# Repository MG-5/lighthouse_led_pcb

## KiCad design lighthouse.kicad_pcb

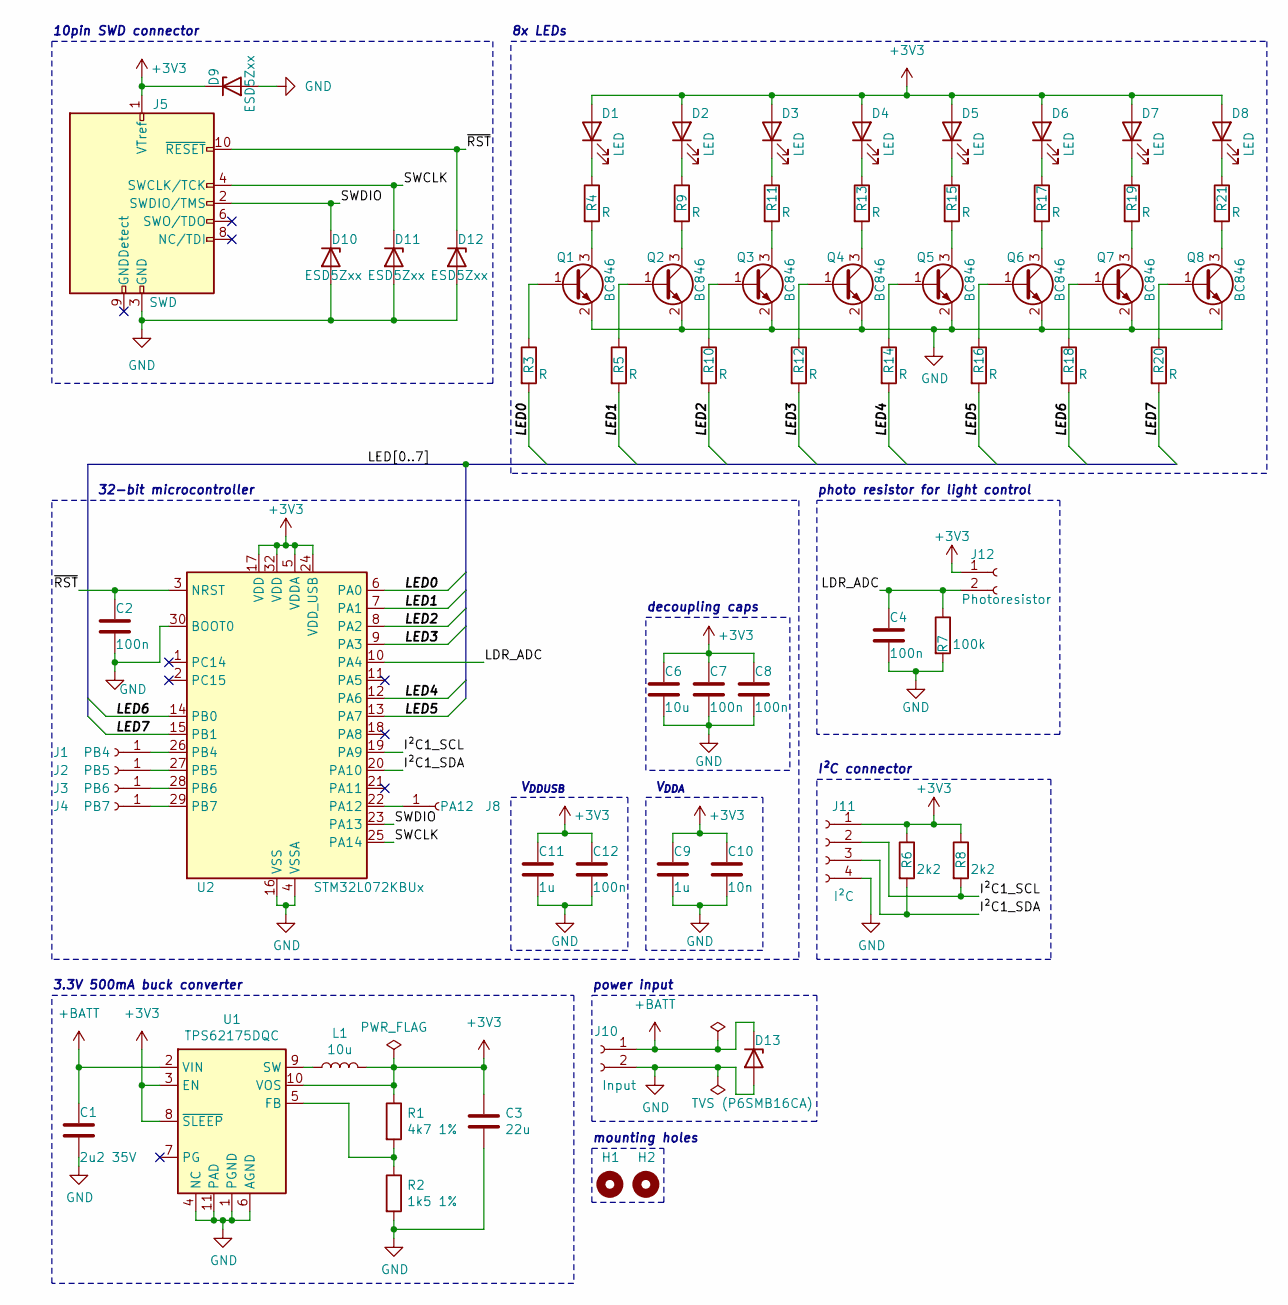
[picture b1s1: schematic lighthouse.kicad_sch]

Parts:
C1: 2u2 35V; C_0603_1608Metric_Pad1.08x0.95mm_HandSolder
C2, C4, C7, C8, C12: 100n; C_0603_1608Metric_Pad1.08x0.95mm_HandSolder
C3: 22u; C_0805_2012Metric_Pad1.18x1.45mm_HandSolder
C6: 10u; C_0805_2012Metric_Pad1.18x1.45mm_HandSolder
C9, C11: 1u; C_0603_1608Metric_Pad1.08x0.95mm_HandSolder
C10: 10n; C_0603_1608Metric_Pad1.08x0.95mm_HandSolder
D1, D2, D3, D4, D5, D6, D7, D8: LED; LED_D5.0mm_Horizontal_O3.81mm_Z3.0mm
D9, D10, D11, D12: ESD5Zxx; D_SOD-523
D13: TVS (P6SMB16CA); D_SMB_Handsoldering
H1, H2: MountingHole; MountingHole_3.2mm_M3_ISO14580
J1: PB4; PinHeader_1x01_P2.54mm_Vertical
J2: PB5; PinHeader_1x01_P2.54mm_Vertical
J3: PB6; PinHeader_1x01_P2.54mm_Vertical
J4: PB7; PinHeader_1x01_P2.54mm_Vertical
J5: SWD; PinHeader_2x05_P1.27mm_Vertical_SMD
J8: PA12; PinHeader_1x01_P2.54mm_Vertical
J10: Input; Molex_PicoBlade_53047-0210_1x02_P1.25mm_Vertical
J11: I²C; Molex_PicoBlade_53047-0410_1x04_P1.25mm_Vertical
J12: Photoresistor; Molex_PicoBlade_53047-0210_1x02_P1.25mm_Vertical
L1: 10u; L_1210_3225Metric
Q1, Q2, Q3, Q4, Q5, Q6, Q7, Q8: BC846; SOT-23
R1: 4k7 1%; R_0603_1608Metric_Pad0.98x0.95mm_HandSolder
R2: 1k5 1%; R_0603_1608Metric_Pad0.98x0.95mm_HandSolder
R3, R4, R5, R9, R10, R11, R12, R13, R14, R15, R16, R17, R18, R19, R20, R21: R; R_0603_1608Metric_Pad0.98x0.95mm_HandSolder
R6, R8: 2k2; R_0603_1608Metric_Pad0.98x0.95mm_HandSolder
R7: 100k; R_0603_1608Metric_Pad0.98x0.95mm_HandSolder
U1: TPS62175DQC; WSON-10-1EP_2x3mm_P0.5mm_EP0.84x2.4mm_ThermalVias
U2: STM32L072KBUx; QFN-32-1EP_5x5mm_P0.5mm_EP3.45x3.45mm

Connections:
+3V3: C3.1, C6.1, C7.1, C8.1, C9.1, C10.1, C11.1, C12.1, D1.2 (A), D2.2 (A), D3.2 (A), D4.2 (A), D5.2 (A), D6.2 (A), D7.2 (A), D8.2 (A), D9.1 (K), J5.1 (VTref), J11.1, J12.1, L1.2, R1.1, R6.1, R8.1, U1.3 (EN), U1.8 (~SLEEP), U1.10 (VOS), U2.5 (VDDA), U2.17 (VDD), U2.24 (VDD_USB), U2.32 (VDD)
+BATT: C1.1, D13.1 (K), J10.1, U1.2 (VIN)
/I²C1_SCL: J11.2, R8.2, U2.19 (PA9)
/I²C1_SDA: J11.3, R6.2, U2.20 (PA10)
/LDR_ADC: C4.1, J12.2, R7.1, U2.10 (PA4)
/LED0: R3.2, U2.6 (PA0)
/LED1: R5.2, U2.7 (PA1)
/LED2: R10.2, U2.8 (PA2)
/LED3: R12.2, U2.9 (PA3)
/LED4: R14.2, U2.12 (PA6)
/LED5: R16.2, U2.13 (PA7)
/LED6: R18.2, U2.14 (PB0)
/LED7: R20.2, U2.15 (PB1)
/SWCLK: D11.1 (K), J5.4 (SWCLK/TCK), U2.25 (PA14)
/SWDIO: D10.1 (K), J5.2 (SWDIO/TMS), U2.23 (PA13)
/~RST: C2.1, D12.1 (K), J5.10 (~RESET), U2.3 (NRST)
GND: C1.2, C2.2, C3.2, C4.2, C6.2, C7.2, C8.2, C9.2, C10.2, C11.2, C12.2, D9.2 (A), D10.2 (A), D11.2 (A), D12.2 (A), D13.2 (A), J5.3 (GND), J5.5 (GND), J10.2, J11.4, Q1.2 (E), Q2.2 (E), Q3.2 (E), Q4.2 (E), Q5.2 (E), Q6.2 (E), Q7.2 (E), Q8.2 (E), R2.2, R7.2, U1.1 (PGND), U1.4 (NC), U1.6 (AGND), U1.11 (PAD), U2.4 (VSSA), U2.16 (VSS), U2.30 (BOOT0), U2.31 (VSS), U2.33 (VSS)
unnamed: D1.1 (K), R4.1
unnamed: D2.1 (K), R9.1
unnamed: D3.1 (K), R11.1
unnamed: D4.1 (K), R13.1
unnamed: D5.1 (K), R15.1
unnamed: D6.1 (K), R17.1
unnamed: D7.1 (K), R19.1
unnamed: D8.1 (K), R21.1
unnamed: J1.1, U2.26 (PB4)
unnamed: J2.1, U2.27 (PB5)
unnamed: J3.1, U2.28 (PB6)
unnamed: J4.1, U2.29 (PB7)
unnamed: J8.1, U2.22 (PA12)
unnamed: Q1.1 (B), R3.1
unnamed: Q1.3 (C), R4.2
unnamed: Q2.1 (B), R5.1
unnamed: Q2.3 (C), R9.2
unnamed: Q3.1 (B), R10.1
unnamed: Q3.3 (C), R11.2
unnamed: Q4.1 (B), R12.1
unnamed: Q4.3 (C), R13.2
unnamed: Q5.1 (B), R14.1
unnamed: Q5.3 (C), R15.2
unnamed: Q6.1 (B), R16.1
unnamed: Q6.3 (C), R17.2
unnamed: Q7.1 (B), R18.1
unnamed: Q7.3 (C), R19.2
unnamed: Q8.1 (B), R20.1
unnamed: Q8.3 (C), R21.2
unnamed: R1.2, R2.1, U1.5 (FB)
unnamed: L1.1, U1.9 (SW)

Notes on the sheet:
power input
mounting holes
3.3V 500mA buck converter
10pin SWD connector
8x LEDs
V_{DDA}
32-bit microcontroller
decoupling caps
V_{DDUSB}
photo resistor for light control
I²C connector

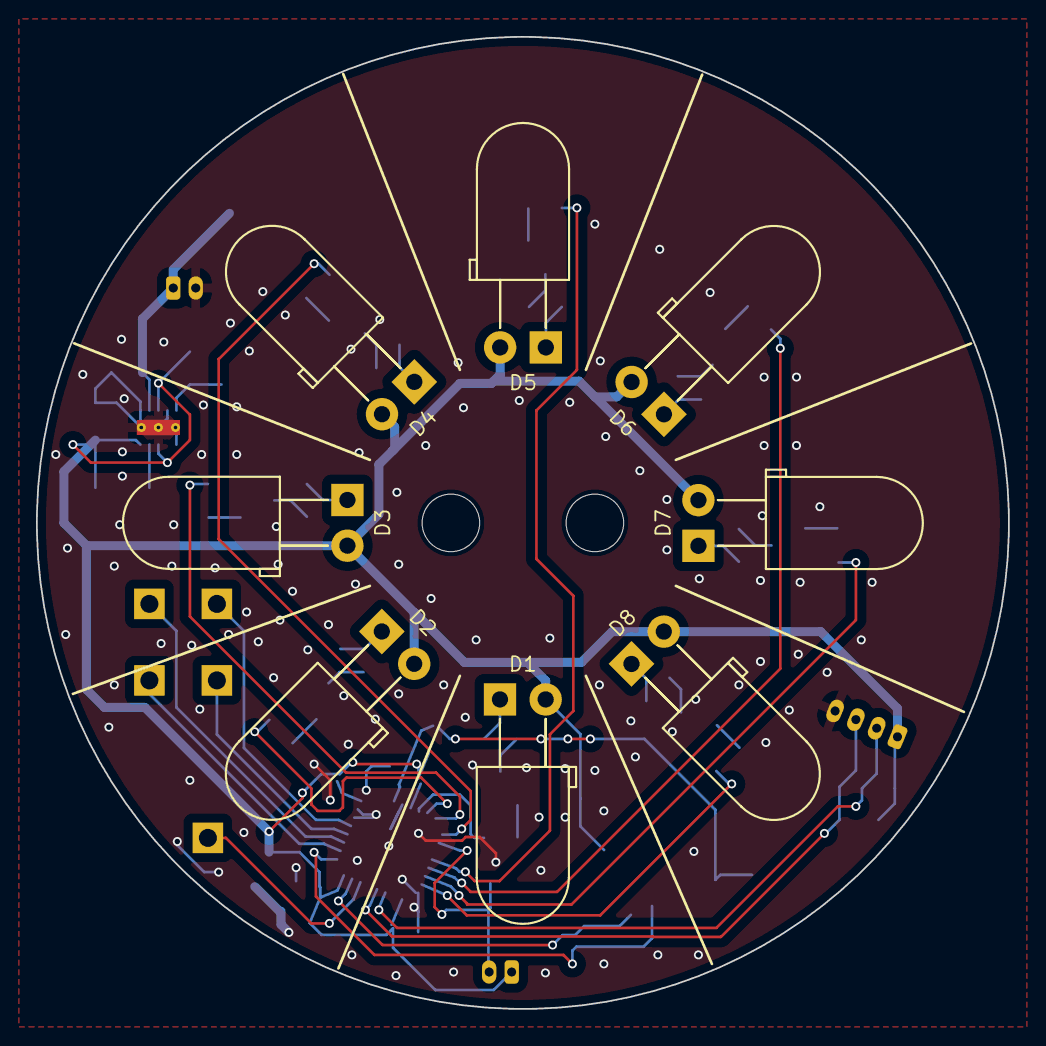
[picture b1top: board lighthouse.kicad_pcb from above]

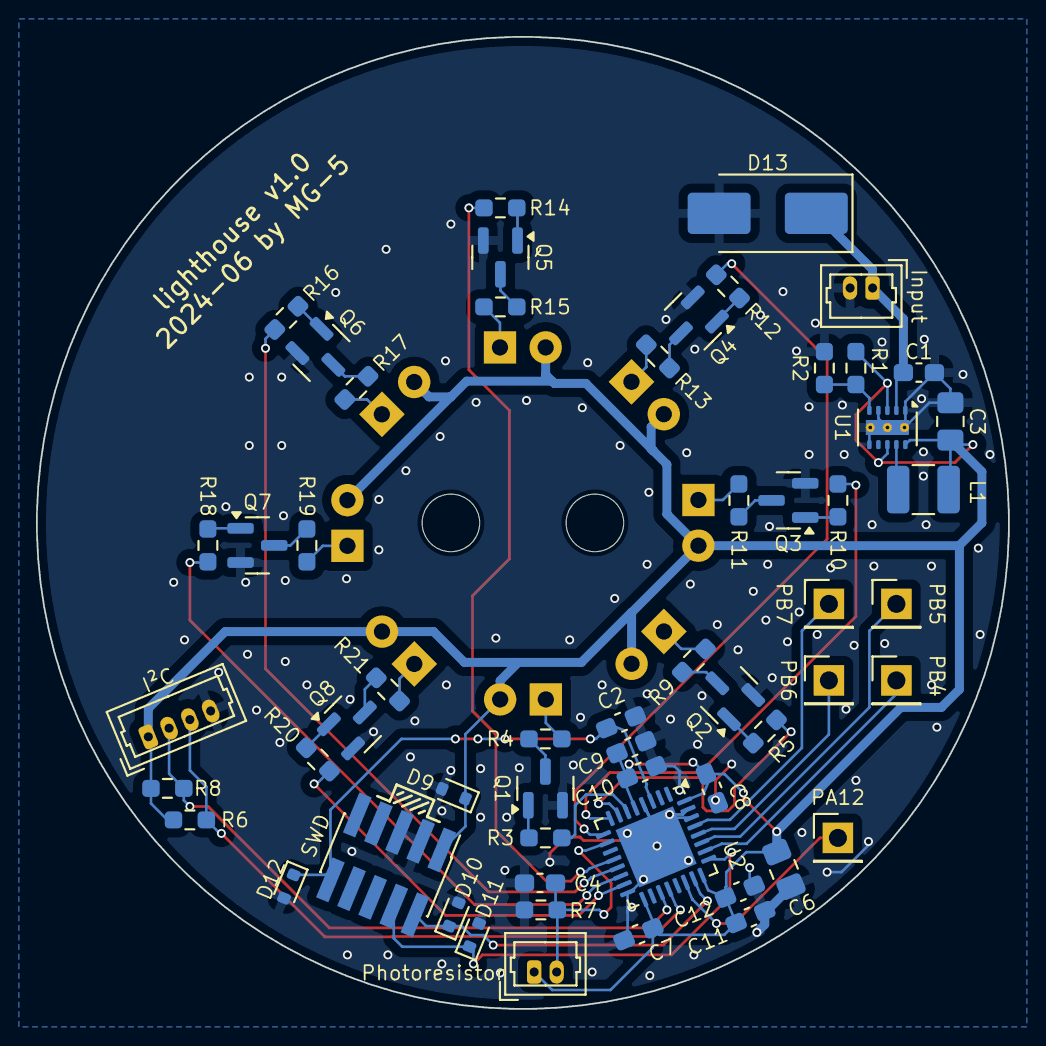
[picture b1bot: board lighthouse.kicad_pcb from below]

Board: 2 copper layers, 54.0 x 54.0 mm, 67 parts (57 on the bottom side), 48 nets.

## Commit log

2024-06-11 Init KiCad project
2024-06-13 Schematic and PCB
